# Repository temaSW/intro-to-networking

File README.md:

# Основы построения инфокоммуникационных сетей и систем

Учебная веб-платформа бакалаврского курса ОПИСиС.

**[Открыть сайт курса](https://temasw.github.io/intro-to-networking/)**

Автор -- Шинкевич А. С.

## О курсе

Платформа предназначена для публикации материалов бакалаврского курса «Основы построения инфокоммуникационных сетей и систем» в виде веб-сайта. Материалы дополняются по мере разработки.

Лекции, практика и справочные страницы содержат интерактивные демонстрации: параметры сигналов и каналов можно менять прямо в браузере и наблюдать результат.

## Содержание

- Лекции, практический материал и справочные страницы в формате QMD; раздел лабораторных работ пока содержит страницу-заготовку.
- JavaScript-модели и интерфейсы интерактивных демонстраций.
- Скрипты генерации иллюстраций и данных, тесты моделей и ресурсов.
- Изображения, аудиоданные, стили и конфигурация сборки и публикации.

## Технологии

Quarto / QMD → HTML · JavaScript (ES-модули) · SCSS / CSS · Python · GitHub Actions · GitHub Pages.

## Структура проекта

```text
.
├── course/                     # Исходники публичного сайта
│   ├── _quarto.yml             # Навигация, темы и параметры сборки
│   ├── index.qmd               # Входная страница
│   ├── lectures/               # Лекции и демонстрации
│   ├── practice/               # Практический материал
│   ├── labs/                   # Заготовка раздела лабораторных
│   ├── reference/              # Справочные страницы
│   ├── interactives/           # Браузерные модели и интерфейсы
│   ├── assets/                 # Иллюстрации и аудиоресурсы
│   ├── data/                   # Табличные данные
│   └── styles/                 # SCSS и CSS
├── interactives/               # Python-модель аудиоканала
├── scripts/                    # Проверка сборки и генерация ресурсов
├── tests/                      # Проверки моделей и статических ресурсов
├── pyproject.toml              # Метаданные Python-проекта
└── .github/workflows/check.yml # Проверка и публикация сайта
```

## Разработка и адаптация

Репозиторий можно форкнуть и адаптировать как основу собственной учебной платформы: заменить QMD-материалы, настроить навигацию и адрес сайта в `course/_quarto.yml`, переиспользовать нужные интерактивные компоненты.

Для локального просмотра установите Quarto **1.10.18**, затем из корня репозитория выполните:

```bash
cd course
quarto preview
```

Для полной сборки и проверки версии Quarto нужен также Python **3.11+**. Из корня репозитория:

```bash
python scripts/check.py
```

Результат сборки -- HTML-сайт в `course/_site/`. Тесты моделей используют `pytest`, `numpy` и Node.js. Из корня репозитория:

```bash
python -m pip install pytest numpy
python -m pytest -q
```

Зависимости отдельной генерации и проверки аудиоданных перечислены в `scripts/requirements-audio.txt`.

## Сборка и публикация

Workflow [Check site](https://github.com/temaSW/intro-to-networking/actions/workflows/check.yml) запускается при push, pull request и вручную. GitHub Actions устанавливает Python 3.11, Quarto 1.10.18, `pytest` и `numpy`, запускает тесты и выполняет `python scripts/check.py` для сборки всего сайта.

После успешных проверок ветки `main` при push или ручном запуске сайт публикуется через GitHub Pages. Pull request и другие ветки проходят проверку без публикации.

## Открыть курс на телефоне

QR-код ведёт на [опубликованный сайт курса](https://temasw.github.io/intro-to-networking/):

## Лицензии

- **[MIT](LICENSE)** -- программный код, скрипты, тесты, стили, конфигурация и техническая документация.
- **[CC BY 4.0](LICENSE)** -- оригинальные учебные тексты, задания, авторские иллюстрации и другие учебные материалы.

В смешанных QMD/HTML-файлах учебное содержимое распространяется по CC BY 4.0, а код -- по MIT. Сторонние материалы сохраняют собственные условия. Точное распределение описано в [LICENSE](LICENSE).

При использовании учебных материалов укажите автора -- Шинкевич А. С., ссылку на источник и CC BY 4.0; при адаптации отметьте изменения.

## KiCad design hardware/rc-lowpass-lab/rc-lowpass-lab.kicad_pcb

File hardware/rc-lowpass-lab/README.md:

# Учебная плата RC-ФНЧ

Пассивная двухслойная плата 33 × 33 мм для опыта с генератором меандра и двухканальным осциллографом. Пять входов дают пять частот среза при одном общем конденсаторе. Все устанавливаемые компоненты выводные. Для компактности отдельные монтажные отверстия не предусмотрены.

## Схема и расчёт

```text
J1 FC_1K  ─ R1 16k ─┐
J2 FC_3K  ─ R2 5k1 ─┤
J3 FC_5K  ─ R3 3k3 ─┤
J4 FC_9K  ─ R4 1k8 ─┼── OUT (J6)
J5 FC_19K ─ R5 820 ─┘       │
                            C1 10 nF
                             │
                       GND (J7, J8, J9)
```

При `C = 10 nF` постоянная времени `τ = RC`, частота среза `fc = 1/(2πRC)`.

| Вход | Резистор | R | C | τ | Расчётная fc |
|---|---|---:|---:|---:|---:|
| J1 | R1 | 16 kΩ | 10 nF | 160 µs | 994,7 Hz ≈ 1 kHz |
| J2 | R2 | 5,1 kΩ | 10 nF | 51 µs | 3 120,7 Hz ≈ 3 kHz |
| J3 | R3 | 3,3 kΩ | 10 nF | 33 µs | 4 822,9 Hz ≈ 5 kHz |
| J4 | R4 | 1,8 kΩ | 10 nF | 18 µs | 8 841,9 Hz ≈ 9 kHz |
| J5 | R5 | 820 Ω | 10 nF | 8,2 µs | 19 409,5 Hz ≈ 19 kHz |

## Подключение и наблюдение

1. Подайте сигнал генератора **только на один** из J1–J5, его землю — на любой из J7–J9. Остальные входы оставьте свободными.
2. Подключите CH1 осциллографа к выбранному входу, CH2 — к `OUT` (J6). Общие провода обоих каналов подключите к `GND` (J7/J8/J9). Третий контакт J9 находится слева от пары J7/J8, поэтому три земляных провода можно подключить одновременно. У сетевого осциллографа земли каналов обычно общие: не цепляйте их к сигнальным точкам.
3. При меандре около 1 kHz сравните амплитуду и форму сигнала на обоих каналах. При `fc≈1 kHz` амплитуда основной гармоники уже уменьшается, фронты сильно округляются. К `fc≈19 kHz` форма приближается к входному меандру, хотя фронты по-прежнему сглажены.

RC-ФНЧ не обрывает спектр на `fc`: амплитуда каждой гармоники уменьшается плавно в зависимости от её частоты. Частота `fc` означает спад амплитуды синусоиды до `1/√2` (около −3 dB), а не полное подавление. Сопоставление с гармониками 1, 3, 5, 9 и 19 в учебной модели является методическим; маркировка входов платы обозначает реальные приблизительные частоты среза.

Выходное сопротивление генератора (например, около 50 Ω) добавляется к сопротивлению выбранной ветви. Для R5 это даёт при идеальных 10 nF `fc≈18,3 kHz` вместо `19,4 kHz`; для ветвей с большим R эффект меньше. Допуски R и C, а также условия работы X7R, дают дополнительное отличие измеренной частоты от расчётной.

## Компоненты и посадочные места

| Обозначения | KiCad footprint | Геометрия |
|---|---|---|
| R1–R5 | `Resistor_THT:R_Axial_DIN0207_L6.3mm_D2.5mm_P7.62mm_Horizontal` | корпус 6,3 × 2,5 мм, шаг отверстий 7,62 мм |
| C1 | `Capacitor_THT:C_Disc_D5.0mm_W2.5mm_P5.00mm` | THT, шаг отверстий 5,00 мм, условный габарит 5 × 2,5 мм |
| J1–J9 | `Connector_PinHeader_2.54mm:PinHeader_1x01_P2.54mm_Vertical` | одиночные штыри, шаг семейства 2,54 мм; расстояние между входами на плате 5,5 мм |

Резисторы — обычные металлоплёночные THT 0,25 W, предпочтительно 1%. Для C1 задан предполагаемый `TS170R1H103K8BBB0R`, X7R, 50 V, ±10%, с ориентировочным шагом выводов 5,08 мм. Выбранный стандартный footprint KiCad имеет шаг 5,00 мм (разница 0,08 мм). Его контур условен для [серии Suntan TS17](https://www.suntan.com.hk/news/Suntan-Multilayer-Axial-Radial-Ceramic-Capacitor-TS17-20230213.html). **Перед заказом компонентов и платы нужно сверить механический чертёж именно поставляемой версии C1** с площадками и контуром; в проекте это единственное не подтверждённое по чертежу посадочное соответствие.

Площадка J6 `OUT` находится рядом с R1, C1 подключён к общей шине рядом с R3, а три площадки земли J7/J8/J9 размещены под C1 и слева от пары J7/J8. Эти точки имеют те же сети `OUT` и `GND`, что на принципиальной схеме. Расстояние по дорожке от входного штыря до площадки резистора — 6,5 мм. Шина `OUT` идёт вертикально прямо через вторые площадки R1–R5, без горизонтальных отводов от резисторов. На обороте — полигон GND; все сигнальные дорожки шириной 0,8 мм идут сверху, переходных отверстий нет. Шелкография показывает `fc≈...`, номиналы R, `OUT`, `GND` и `C = 10 nF`.

## Проверка и файлы

Проверено KiCad CLI 10.0.5: ERC — 0 ошибок/предупреждений; DRC — 0 нарушений, 0 незаведённых площадок, 0 ошибок корпусов. Схемный netlist содержит пять отдельных входных сетей, общую `OUT` и `GND`; все три контакта J7/J8/J9 имеют сеть GND. Вид сверху и 3D-рендер KiCad проверены визуально. Экспорт Gerber содержит все шесть необходимых слоёв и сверловку (21 металлизированное отверстие, без переходных). Перед заказом следует проверить Gerber в просмотрщике изготовителя; верхние дорожки не доходят до краёв платы, а нижний полигон отступает на 0,5 мм. Все слои экспортированы KiCad в одной системе координат (`SameCoordinates=Original`).

- `rc-lowpass-lab.kicad_pro`, `.kicad_sch`, `.kicad_pcb` — редактируемый проект KiCad.
- `BOM.csv` — список деталей.
- `build.py` — текстовый генератор исходников для воспроизводимости, требует Python из комплекта KiCad 10.
- `erc.txt`, `drc.txt` — отчёты KiCad CLI.
- `preview/pcb-crop.png` — вид верхней стороны для проверки маркировки и третьего GND.
- `preview/pcb-3d.png`, `preview/pcb-3d.glb` — изображение 3D-вида и интерактивная 3D-модель KiCad.
- `gerbers/` — слои Gerber, сверловка и ZIP; перед заказом повторно проверьте C1 и правила конкретной фабрики.

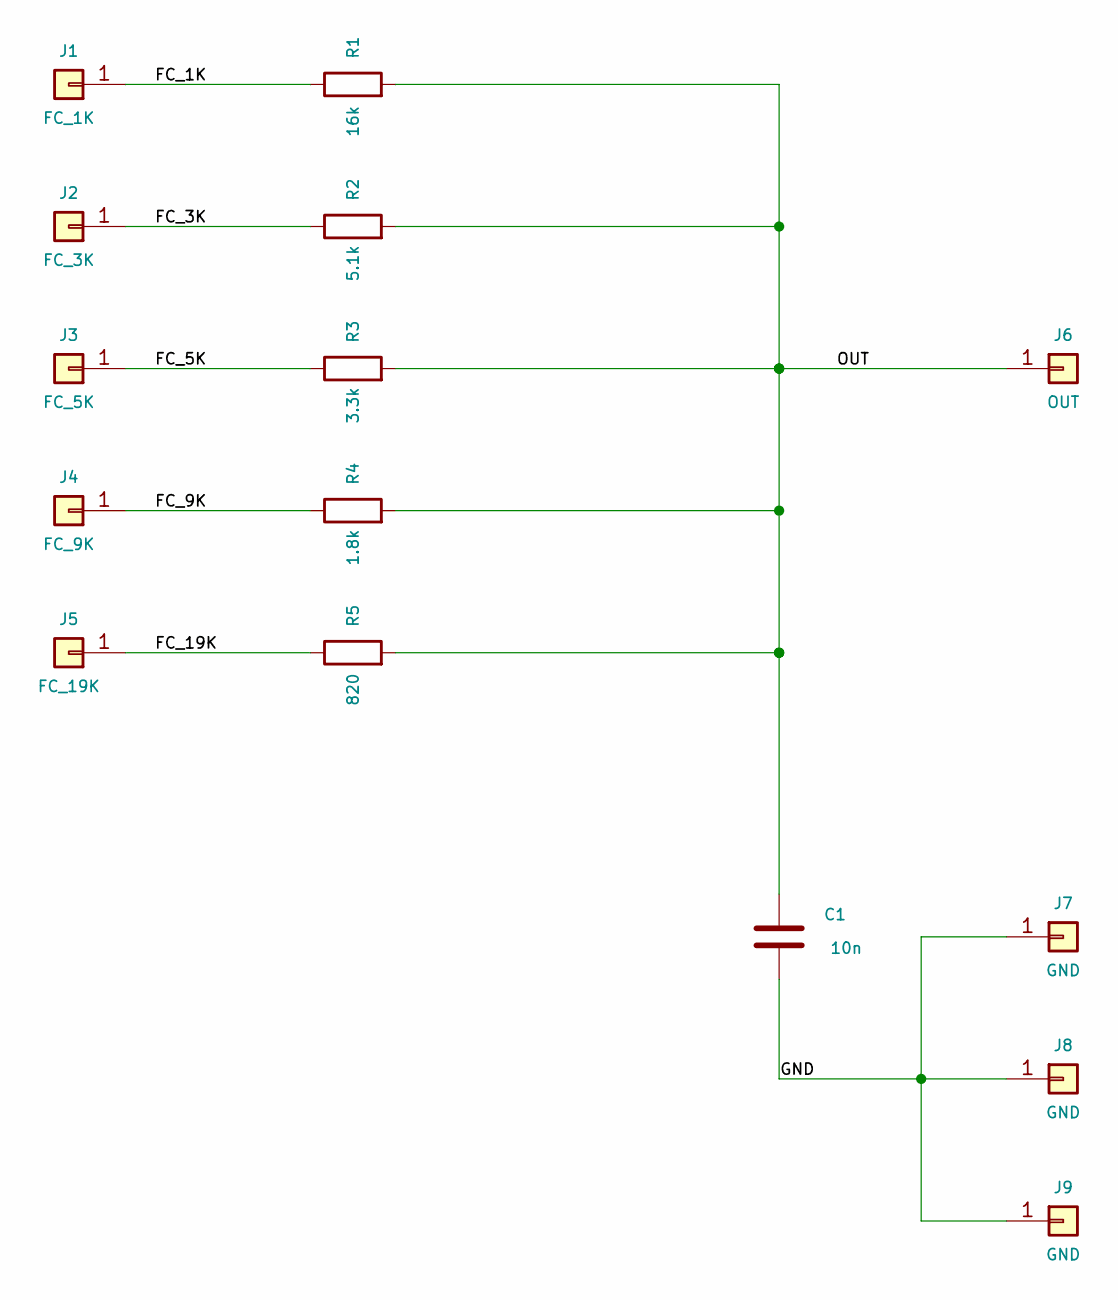
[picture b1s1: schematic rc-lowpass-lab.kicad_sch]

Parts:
C1: 10n; C_Disc_D5.0mm_W2.5mm_P5.00mm; MPN TS170R1H103K8BBB0R
J1: FC_1K; PinHeader_1x01_P2.54mm_Vertical
J2: FC_3K; PinHeader_1x01_P2.54mm_Vertical
J3: FC_5K; PinHeader_1x01_P2.54mm_Vertical
J4: FC_9K; PinHeader_1x01_P2.54mm_Vertical
J5: FC_19K; PinHeader_1x01_P2.54mm_Vertical
J6: OUT; PinHeader_1x01_P2.54mm_Vertical
J7, J8, J9: GND; PinHeader_1x01_P2.54mm_Vertical
R1: 16k; R_Axial_DIN0207_L6.3mm_D2.5mm_P7.62mm_Horizontal
R2: 5.1k; R_Axial_DIN0207_L6.3mm_D2.5mm_P7.62mm_Horizontal
R3: 3.3k; R_Axial_DIN0207_L6.3mm_D2.5mm_P7.62mm_Horizontal
R4: 1.8k; R_Axial_DIN0207_L6.3mm_D2.5mm_P7.62mm_Horizontal
R5: 820; R_Axial_DIN0207_L6.3mm_D2.5mm_P7.62mm_Horizontal

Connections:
FC_1K: J1.1, R1.1
FC_3K: J2.1, R2.1
FC_5K: J3.1, R3.1
FC_9K: J4.1, R4.1
FC_19K: J5.1, R5.1
GND: C1.2, J7.1, J8.1, J9.1
OUT: C1.1, J6.1, R1.2, R2.2, R3.2, R4.2, R5.2

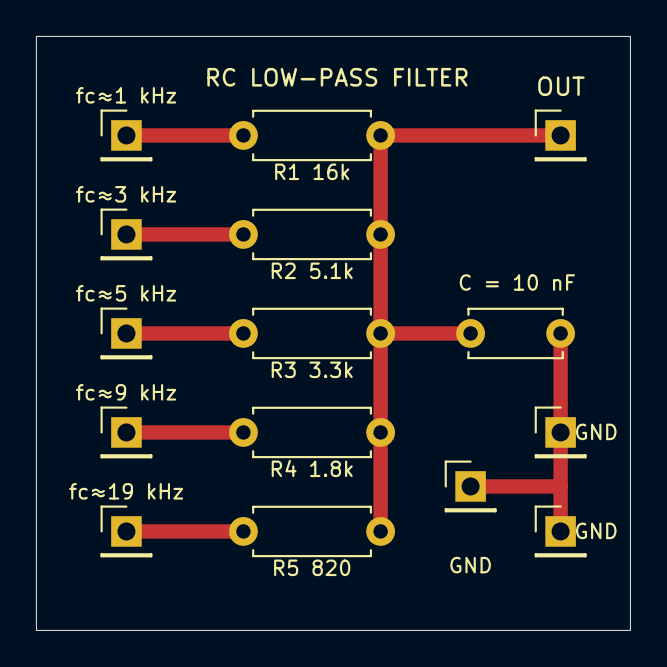
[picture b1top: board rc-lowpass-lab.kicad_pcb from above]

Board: 2 copper layers, 33.0 x 33.0 mm, 15 parts (0 on the bottom side), 7 nets.
